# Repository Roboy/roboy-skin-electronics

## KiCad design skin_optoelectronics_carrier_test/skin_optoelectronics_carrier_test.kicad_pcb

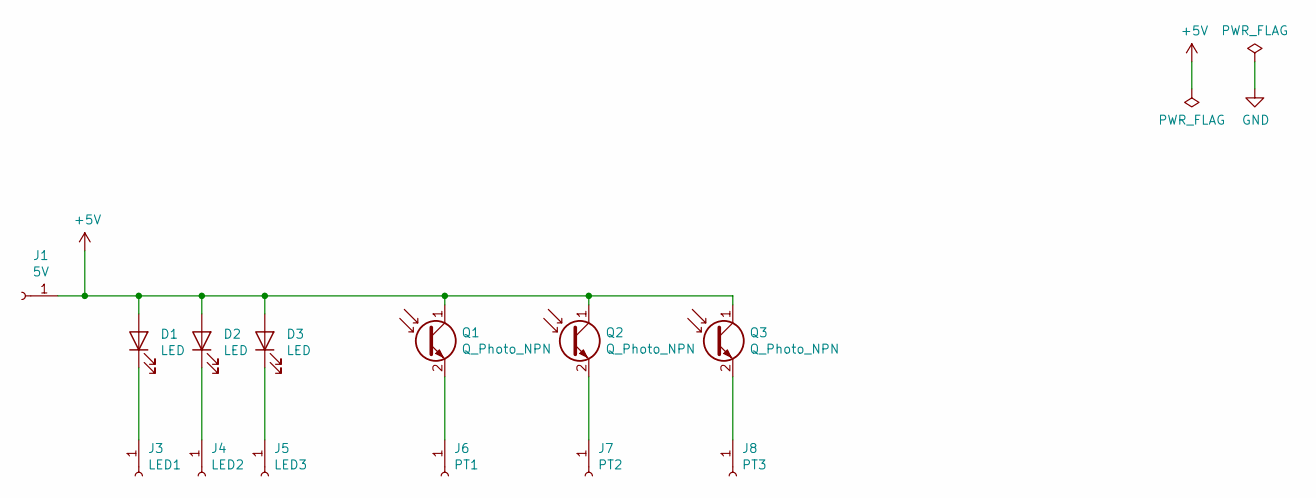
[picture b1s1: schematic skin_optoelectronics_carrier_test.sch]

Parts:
D1, D2, D3: LED; Everlight_3x2x1_side_lens_wide_LED
J1: 5V; TestPoint_Pad_D1.5mm
J3: LED1; TestPoint_Pad_D1.5mm
J4: LED2; TestPoint_Pad_D1.5mm
J5: LED3; TestPoint_Pad_D1.5mm
J6: PT1; TestPoint_Pad_D1.5mm
J7: PT2; TestPoint_Pad_D1.5mm
J8: PT3; TestPoint_Pad_D1.5mm
Q1, Q2, Q3: Q_Photo_NPN; Everlight_3x2x1_side_lens_wide_Phototransistor

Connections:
+5V: D1.2 (A), D2.2 (A), D3.2 (A), J1.1, Q1.1 (C), Q2.1 (C), Q3.1 (C)
unnamed: D1.1 (K), J3.1
unnamed: D2.1 (K), J4.1
unnamed: D3.1 (K), J5.1
unnamed: J6.1, Q1.2 (E)
unnamed: J7.1, Q2.2 (E)
unnamed: J8.1, Q3.2 (E)

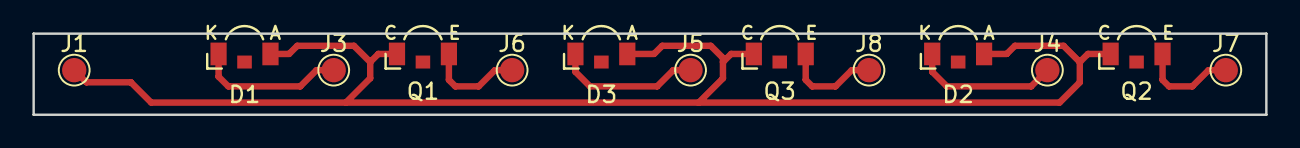
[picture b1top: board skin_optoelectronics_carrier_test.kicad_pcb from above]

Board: 2 copper layers, 76.0 x 5.0 mm, 13 parts (0 on the bottom side), 7 nets.

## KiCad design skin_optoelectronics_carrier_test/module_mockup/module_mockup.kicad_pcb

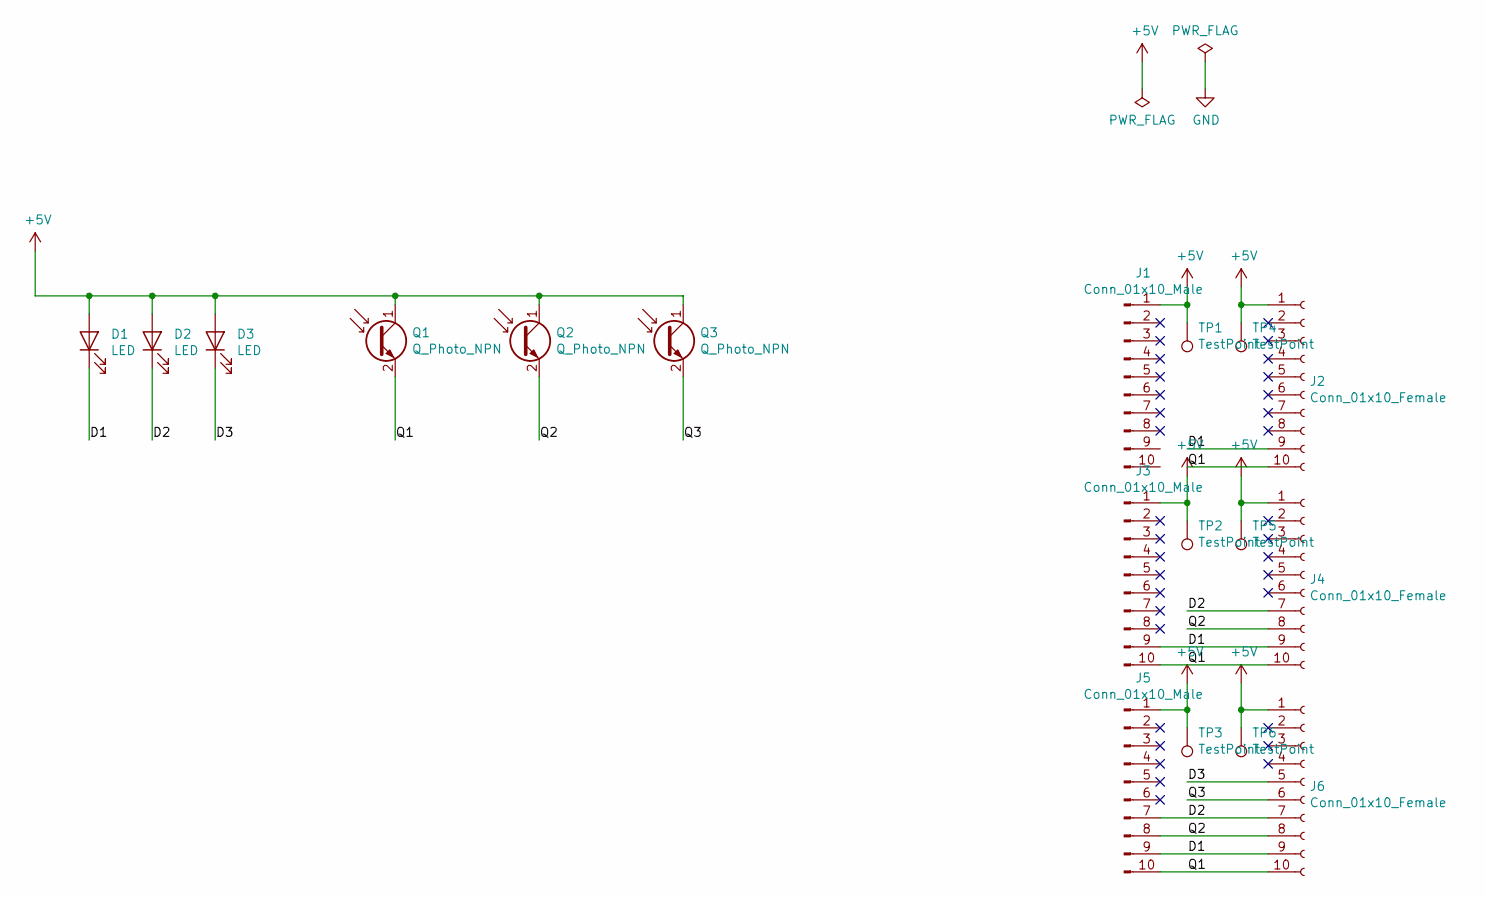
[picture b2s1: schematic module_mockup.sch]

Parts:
D1, D2, D3: LED; Everlight_3x2x1_side_lens_wide_LED
J1, J3, J5: Conn_01x10_Male; FPC_0.5mmx10
J2, J4, J6: Conn_01x10_Female; FPC_0.5mmx10
Q1, Q2, Q3: Q_Photo_NPN; Everlight_3x2x1_side_lens_wide_Phototransistor
TP1, TP2, TP3, TP4, TP5, TP6: TestPoint; TestPoint_Pad_D1.0mm

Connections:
+5V: D1.2 (A), D2.2 (A), D3.2 (A), J1.1, J2.1, J3.1, J4.1, J5.1, J6.1, Q1.1 (C), Q2.1 (C), Q3.1 (C), TP1.1, TP2.1, TP3.1, TP4.1, TP5.1, TP6.1
/D1: D1.1 (K), J2.9, J3.9, J4.9, J5.9, J6.9
/D2: D2.1 (K), J4.7, J5.7, J6.7
/D3: D3.1 (K), J6.5
/Q1: J2.10, J3.10, J4.10, J5.10, J6.10, Q1.2 (E)
/Q2: J4.8, J5.8, J6.8, Q2.2 (E)
/Q3: J6.6, Q3.2 (E)

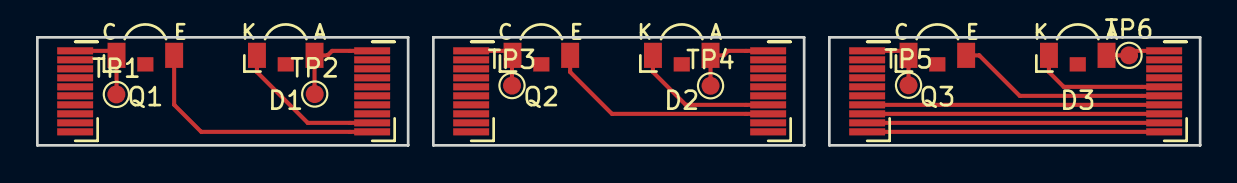
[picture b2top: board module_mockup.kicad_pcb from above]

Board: 2 copper layers, 64.6 x 6.0 mm, 18 parts (0 on the bottom side), 7 nets.

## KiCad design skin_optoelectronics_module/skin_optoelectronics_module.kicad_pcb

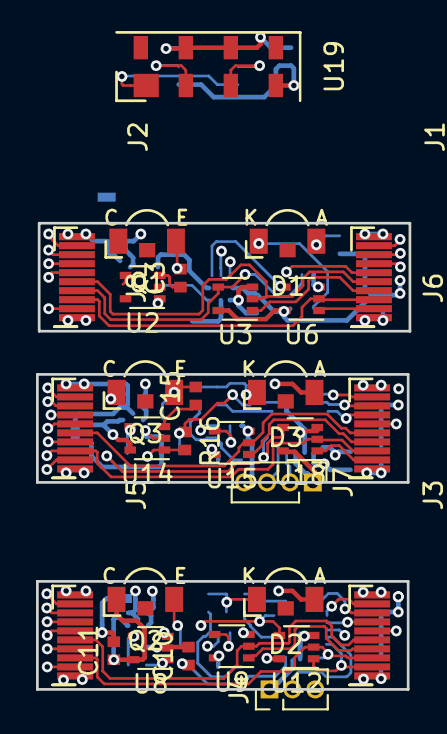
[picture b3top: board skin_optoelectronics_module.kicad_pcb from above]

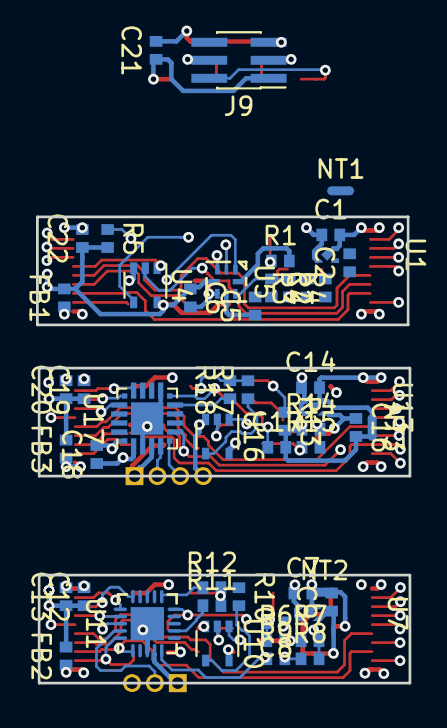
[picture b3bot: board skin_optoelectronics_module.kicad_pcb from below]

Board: 4 copper layers, 20.7 x 25.9 mm, 80 parts (51 on the bottom side), 70 nets.

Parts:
C1, C2, C7, C9, C12, C14, C16, C19, C22: 1u; The_0402_FP
C3, C8, C15: optional_0; The_0402_FP
C4, C10, C17: 100p; The_0402_FP
C5, C6, C11, C13, C18, C20, C21: 100n; The_0402_FP
D1, D2, D3: LED; Everlight_3x2x1_side_lens_wide_LED
FB1, FB2, FB3: Ferrite_Bead; The_0402_FP
J1, J3, J6: Conn_01x10_Female; FPC_0.5mmx10
J2, J5, J8: Conn_01x10_Male; FPC_0.5mmx10
J4: Conn_01x03_Female; PinHeader_1x03_P1.27mm_Vertical
J7: Conn_01x04_Female; PinHeader_1x04_P1.27mm_Vertical
J9: Conn_01x05_Female; PinHeader_2x03_P1.00mm_Vertical_SMD
NT1, NT2, NT3: Net-Tie_2; NetTie-2_SMD_Pad0.5mm
Q1, Q2, Q3: Q_Photo_NPN; Everlight_3x2x1_side_lens_wide_Phototransistor
R1, R6, R13: 10k; The_0402_FP
R2, R7, R14: optional; The_0402_FP
R3, R8, R15: optional_0; The_0402_FP
R4, R5, R9, R10, R11, R12, R16, R17, R18: 1k; The_0402_FP
U1, U7, U13: MIC5317-3.3YMT-TZ; 4-DFN
U2, U8, U14: OPA340NA; SOT-353_SC-70-5
U3, U6, U9, U12, U15, U18: 74LVC1G79; SOT-353_SC-70-5
U4, U10, U16: 74LVC1G125; SOT-353_SC-70-5
U5: ADS7042; X2QFN-8
U11: ATtiny416; UQFN-20-1EP_3x3mm_P0.4mm_EP1.85x1.85mm
U17: EFM8BB10F2G-A-QFN20; SiliconLabs_QFN-20-1EP_3x3mm_P0.5mm
U19: TSL1401CL

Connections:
+3V3: C21.1, J9.1, U19.4
+5V: C1.1, C6.1, C7.1, C12.1, C13.1, C14.1, C19.1, C20.1, C22.1, D2.2, D3.2, FB1.2, FB2.2, FB3.2, J4.1, J7.1, R5.2, U1.3, U1.4, U3.5, U4.5, U5.4, U6.5, U7.3, U7.4, U9.5, U10.5, U11.4, U12.5, U13.3, U13.4, U15.5, U16.5, U17.4, U18.5
/Dual_FF_ADC/AVDD: C2.1, C5.1, Q1.1, U1.1, U2.5, U5.6
/Dual_FF_ADC/Blank: J1.6, J2.6, U4.1
/Dual_FF_ADC/Clk_L: J1.5, J2.5, U3.2
/Dual_FF_ADC/Clk_S: J1.3, J2.3, U6.2
/Dual_FF_ADC/DL_IN: J1.4, U3.1
/Dual_FF_ADC/DL_OUT: J2.4, U3.4, U4.2
/Dual_FF_ADC/DS_IN: J1.2, U6.1
/Dual_FF_ADC/DS_OUT: J2.2, U5.1, U6.4
/Dual_FF_ADC/SCLK: J1.8, J2.8, U5.3
/Dual_FF_ADC/SDI: J1.7, J2.7
/Dual_FF_ADC/SDO: J1.9, J2.9, U5.2
/FF_Attiny416/AVDD: C9.1, C11.1, Q2.1, U7.1, U8.5
/FF_Attiny416/Blank: J3.6, J5.6, U10.1
/FF_Attiny416/Clk_L: J3.5, J5.5, U9.2
/FF_Attiny416/Clk_S: J3.3, J5.3, U11.1, U12.2
/FF_Attiny416/DL_IN: J3.4, U9.1
/FF_Attiny416/DL_OUT: J5.4, U9.4, U10.2
/FF_Attiny416/DS_IN: J3.2, U11.20, U12.1
/FF_Attiny416/DS_OUT: J5.2, U11.10, U11.18, U12.4
/FF_Attiny416/SCLK: J3.8, J5.8, U11.15
/FF_Attiny416/SDI: J3.7, J5.7, U11.17
/FF_Attiny416/SDO: J3.9, J5.9, U11.16
/FF_Attiny416/UPDI: J4.2, U11.19
/FF_EFM8BB1/AVDD: C16.1, C18.1, Q3.1, U13.1, U14.5, U17.2
/FF_EFM8BB1/A_out: C17.1, R16.1, U17.11
/FF_EFM8BB1/Blank: J6.6, J8.6, U16.1
/FF_EFM8BB1/C2CK: J7.2, U17.5
/FF_EFM8BB1/C2D: J7.3, U17.6
/FF_EFM8BB1/Clk_L: J6.5, J8.5, U15.2
/FF_EFM8BB1/Clk_S: J6.3, J8.3, U18.2
/FF_EFM8BB1/DL_IN: J6.4, U15.1
/FF_EFM8BB1/DL_OUT: J8.4, U15.4, U16.2
/FF_EFM8BB1/DS_IN: J6.2, U18.1
/FF_EFM8BB1/DS_OUT: J8.2, U17.7, U18.4
/FF_EFM8BB1/SCLK: J6.8, J8.8, U17.16
/FF_EFM8BB1/SDI: J6.7, J8.7, U17.17
/FF_EFM8BB1/SDO: J6.9, J8.9, U17.15
/Linear_image_sensor./AO: J9.4, U19.3
/Linear_image_sensor./LS_CLK: J9.3, U19.2
/Linear_image_sensor./SI: J9.2, U19.1
GND: C1.2, C6.2, C7.2, C12.2, C13.2, C14.2, C19.2, C20.2, C22.2, J1.10, J2.10, J3.10, J4.3, J5.10, J6.10, J7.4, J8.10, NT1.1, NT2.1, NT3.1, U1.2, U1.5, U3.3, U4.3, U5.5, U6.3, U7.2, U7.5, U9.3, U10.3, U11.3, U11.21, U12.3, U13.2, U13.5, U15.3, U16.3, U17.3, U17.12, U17.21, U18.3
GNDA: C2.2, C4.2, C5.2, C9.2, C10.2, C11.2, C16.2, C17.2, C18.2, C21.2, J9.5, NT1.2, NT2.2, NT3.2, R1.2, R2.1, R6.2, R7.1, R13.2, R14.1, U2.2, U5.8, U8.2, U14.2, U17.1, U19.6, U19.7
unnamed: C3.1, U2.3
unnamed: C3.2, Q1.2, R1.1
unnamed: C4.1, R4.1, U5.7
unnamed: C8.1, U8.3
unnamed: C8.2, Q2.2, R6.1
unnamed: C10.1, R9.1, U11.5
unnamed: C15.1, U14.3
unnamed: C15.2, Q3.2, R13.1
unnamed: D1.1, U4.4
unnamed: D1.2, R5.1
unnamed: D2.1, R10.1, R11.2, R12.2
unnamed: D3.1, R17.2, R18.2
unnamed: FB1.1, J1.1, J2.1
unnamed: FB2.1, J3.1, J5.1
unnamed: FB3.1, J6.1, J8.1
unnamed: R2.2, R3.2, U2.4
unnamed: R3.1, R4.2, U2.1
unnamed: R7.2, R8.2, U8.4
unnamed: R8.1, R9.2, U8.1
unnamed: R10.2, U10.4
unnamed: R11.1, U11.7
unnamed: R12.1, U11.11
unnamed: R14.2, R15.2, U14.4
unnamed: R15.1, R16.2, U14.1
unnamed: R17.1, U16.4
unnamed: R18.1, U17.10

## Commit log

2019-01-22 Initial commit with the prototypes for the skin electronics. In carrier_test are some mockup boards for testing molding and integration with the silicones. Whereas in the optoelectronics_module folde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
